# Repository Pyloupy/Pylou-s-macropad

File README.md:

# Pylou-s-macropad
A custom macropad for the awesome project hackpad! Using a screen 4 keys a knob and a bunch of LEDs, i'll try to develop a custom firmware with KMK to configure a bunch of things (that doesn't mean anything yet) from your PC!

## CAD

My beautiful Case for this keyboard :). top and bot part fits together with simple M3 screws and heatset inserts and all 4 corners and one screw for the pcb. (I didn't add extra photos to show how it'll fit because its='s pretty self explanatory)

There's also diffuser that'll be simple 1-2mm plane of white PLA, they'll be glued to the top part!

Made with SOLIDWORKS (superior to Fusion360 :)) and it's the first time im designing a piece with it (in the past i was using blender for 3d printing ;-;), I hope it works!

## PCB
I used KiCad (for the first time) and i tried to make a compact and clean pcb with small reference and private jokes with my friends!

## Firmware
Made in KMK by reading docs, tutorials from [this guy](https://www.youtube.com/watch?v=PKTRkv8d0NU&list=PLtl-yze0Zzkm5n2ajJRUL48EyCyUgsXf6) (he's great) and a bit of gemini.

It's pretty simple for the moment, but i plan on addings multiples features to configure what keys does what (from your pc), change whats on the screen, show the time, rgb modes etc when i'll build the pad. I'll update the code when everything will be done! 

## BOM
Here's the list of parts for my project!

 - 1x Seeed XIAO RP2040
 - 4x Through-hole 1N4148 Diodes
 - 4x MX-Style switches
 - 1x EC11 Rotary encoders
 - 1x 0.91 inch OLED displays
 - 4x Blank DSA keycaps (White)
 - 10x SK6812 MINI-E LEDs
 - 5x M3x16mm screws
 - 5x M3x5mx4mm heatset inserts
 - 1x 3D printed case: top pink and the rest white

## Special Thanks!
My appreciation to the opheuspad project wich helped me many times! and to the hacklab community very responsive and kind!

PS: I'm french, so forgive me for any english syntax errors :)

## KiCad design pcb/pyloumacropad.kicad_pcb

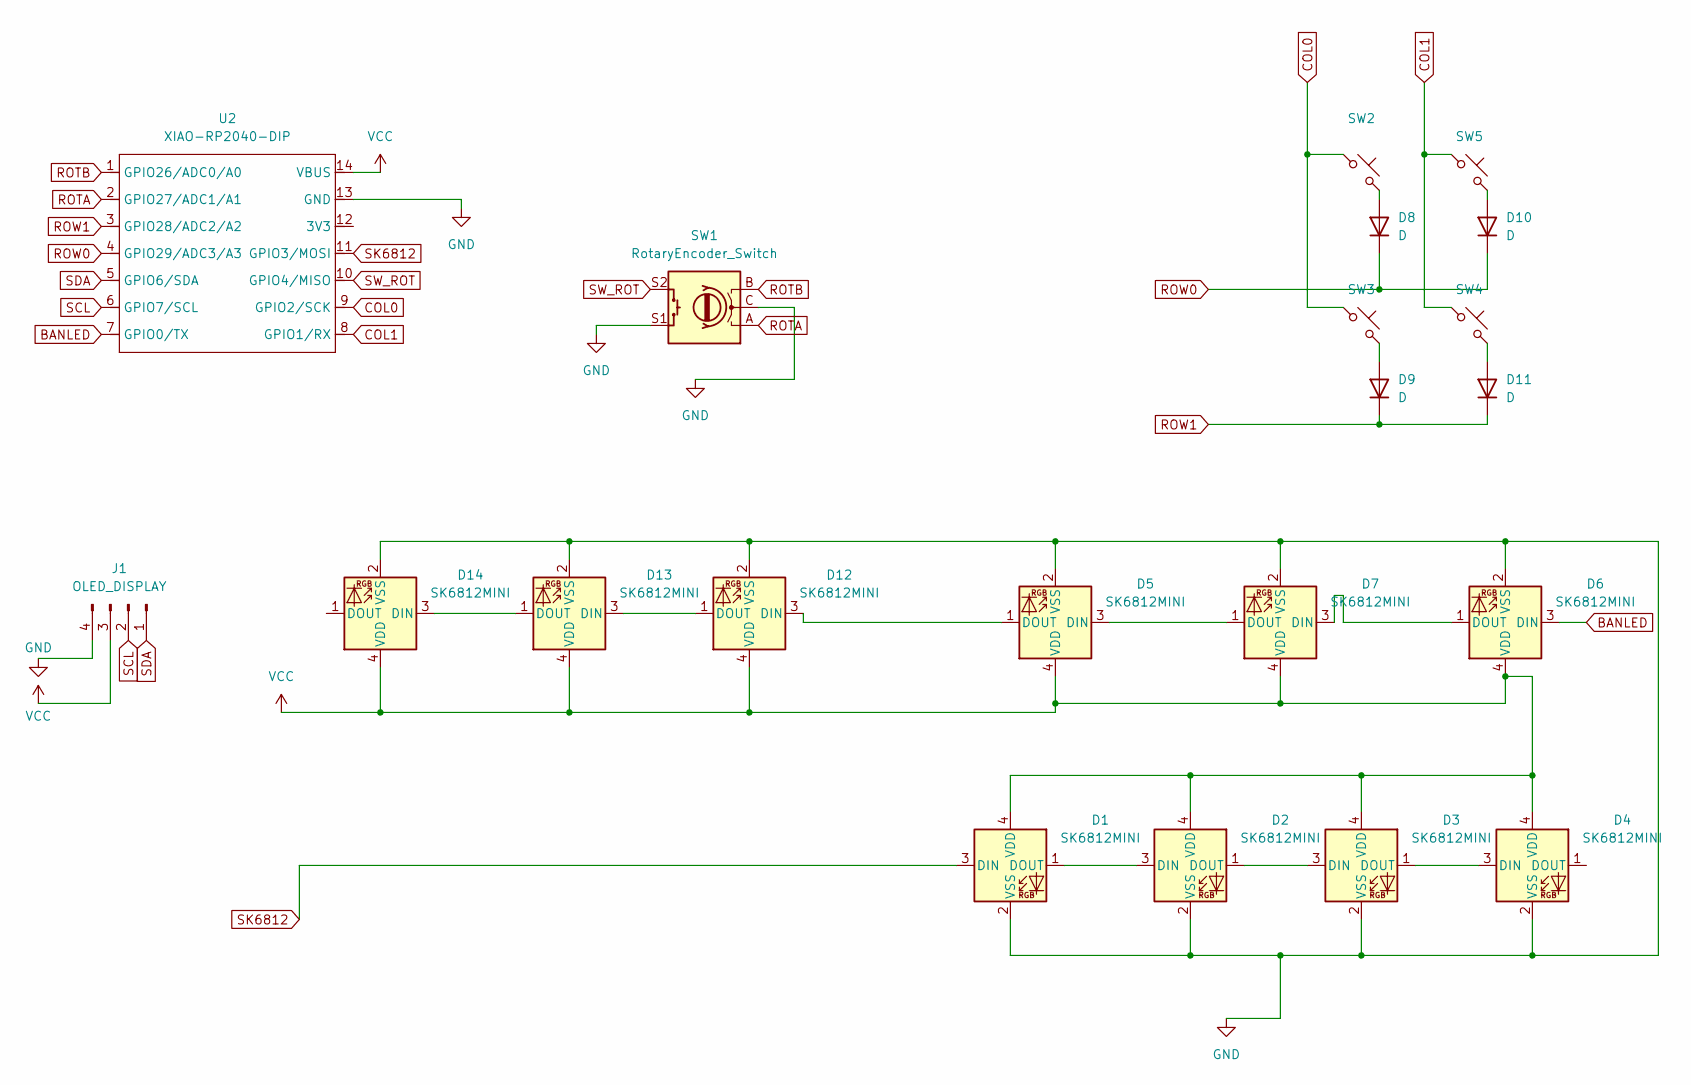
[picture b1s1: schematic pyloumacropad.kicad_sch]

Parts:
D1, D2, D3, D4, D5, D6, D7, D12, D13, D14: SK6812MINI; LED_SK6812MINI_PLCC4_3.5x3.5mm_P1.75mm
D8, D9, D10, D11: D; D_DO-35_SOD27_P7.62mm_Horizontal
J1: OLED_DISPLAY; PinHeader_1x04_P2.54mm_Vertical
SW1: RotaryEncoder_Switch; RotaryEncoder_Alps_EC11E-Switch_Vertical_H20mm
SW2, SW3, SW4, SW5: SW_Push_45deg; SW_Cherry_MX_1.00u_PCB
U2: XIAO-RP2040-DIP

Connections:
BANLED: D6.3 (DIN), U2.7 (GPIO0/TX)
COL0: SW2.1, SW3.1, U2.9 (GPIO2/SCK)
COL1: SW4.1, SW5.1, U2.8 (GPIO1/RX)
GND: D1.2 (VSS), D2.2 (VSS), D3.2 (VSS), D4.2 (VSS), D5.2 (VSS), D6.2 (VSS), D7.2 (VSS), D12.2 (VSS), D13.2 (VSS), D14.2 (VSS), J1.4, SW1.C, SW1.S1, U2.13 (GND)
unnamed: D1.1 (DOUT), D2.3 (DIN)
unnamed: D2.1 (DOUT), D3.3 (DIN)
unnamed: D3.1 (DOUT), D4.3 (DIN)
unnamed: D5.3 (DIN), D7.1 (DOUT)
unnamed: D6.1 (DOUT), D7.3 (DIN)
unnamed: D8.2 (A), SW2.2
unnamed: D9.2 (A), SW3.2
unnamed: D10.2 (A), SW5.2
unnamed: D11.2 (A), SW4.2
unnamed: D5.1 (DOUT), D12.3 (DIN)
unnamed: D12.1 (DOUT), D13.3 (DIN)
unnamed: D13.1 (DOUT), D14.3 (DIN)
ROTA: SW1.A, U2.2 (GPIO27/ADC1/A1)
ROTB: SW1.B, U2.1 (GPIO26/ADC0/A0)
ROW0: D8.1 (K), D10.1 (K), U2.4 (GPIO29/ADC3/A3)
ROW1: D9.1 (K), D11.1 (K), U2.3 (GPIO28/ADC2/A2)
SCL: J1.2, U2.6 (GPIO7/SCL)
SDA: J1.1, U2.5 (GPIO6/SDA)
SK6812: D1.3 (DIN), U2.11 (GPIO3/MOSI)
SW_ROT: SW1.S2, U2.10 (GPIO4/MISO)
VCC: D1.4 (VDD), D2.4 (VDD), D3.4 (VDD), D4.4 (VDD), D5.4 (VDD), D6.4 (VDD), D7.4 (VDD), D12.4 (VDD), D13.4 (VDD), D14.4 (VDD), J1.3, U2.14 (VBUS)

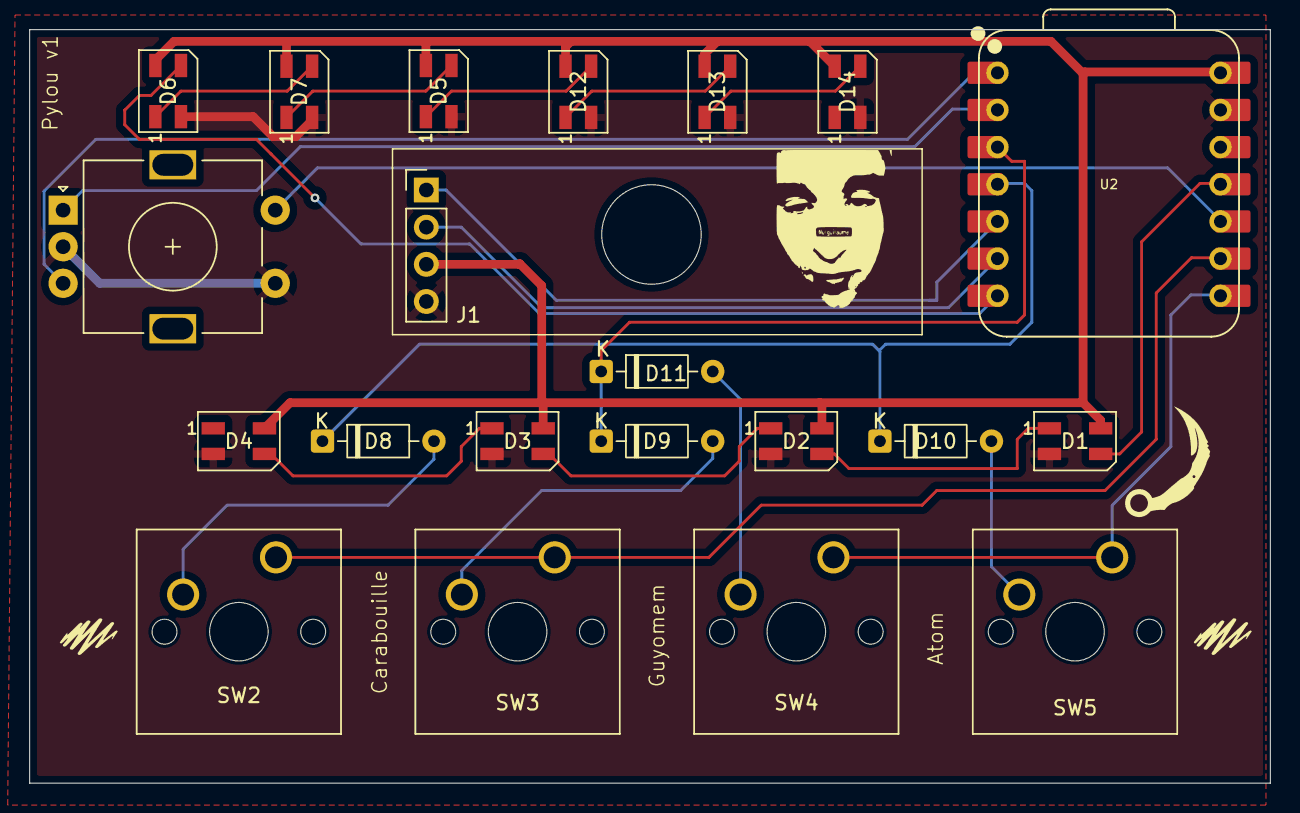
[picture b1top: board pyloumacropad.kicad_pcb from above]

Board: 2 copper layers, 84.8 x 51.5 mm, 21 parts (0 on the bottom side), 25 nets.

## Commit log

2025-12-26 Add detailed project information to README
    Expanded README with CAD, PCB, Firmware, and BOM sections.
2025-12-26 Rename image.png to cad.png
2025-12-26 Rename image.png to pcb.png
2025-12-26 Rename image.png to pcbsch.png
2025-12-26 Update README with neopixel library information
    Added a note about the neopixel library requirement.
2025-12-26 Rename image.png to cadopen.png
